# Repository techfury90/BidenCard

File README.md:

# Biden Card
Partially cost reduced/modernized Sinclair QL Trump Card clone with bonus Dark Brandon meme.

# Background
I originally started this project in late 2023 because real Trump Cards were getting difficult to obtain, and I wanted one for my QLs. 

Alvaro had previously successfully cloned the board, but there were timing-related issues with substituting the PALs for GALs. Analysis of the situation revealed that the issue related to DRAM control timing. Since 41256 DRAM is no longer made, I decided to move to AS6C4008 4mbit SRAM. The resulting logic simplification also eliminated the need for GAL 2, and paring down GAL 1's DRAM-related functions allowed me to fit the new SRAM decode logic into GAL 1, thereby eliminating GAL 2 entirely. 

The end result is 100% compatible with the Trump Card, but only costs about $50 USD to manufacture.

This design is a bit quick/rudimentary/slapdash- in particular, these low-hanging fruits exist for optimization: 
- Replace DIP AS6C4008s with suitable SMD SRAM. Do note that I grounded out OE (output enable) and use only CS to access the SRAM- most SRAMs can handle this but please check the datasheet!
- Redo axial caps with radials (this was really just cargo-culted from the original design to get a viable prototype working quickly)
- Replace 7805 with a more efficient regulator (even with the 7805, however, power consumption is a fraction of the original Trump Card!)

# Credits
- Alvaro Alea for reverse engineering the Trump Card 2 schematic (the basis of this project)
- Tetroid for reverse engineering the PAL/GAL logic equations. His equations were the basis of mine, particularly in regards to the P13/P16 ROM shadowing bodge needed to make pre-Minerva ROMs recognize the ROM.
- Compgeke for doing the PCB layout (I have not quite honed that skill yet... this is my first DIY PCB project of this scale!)

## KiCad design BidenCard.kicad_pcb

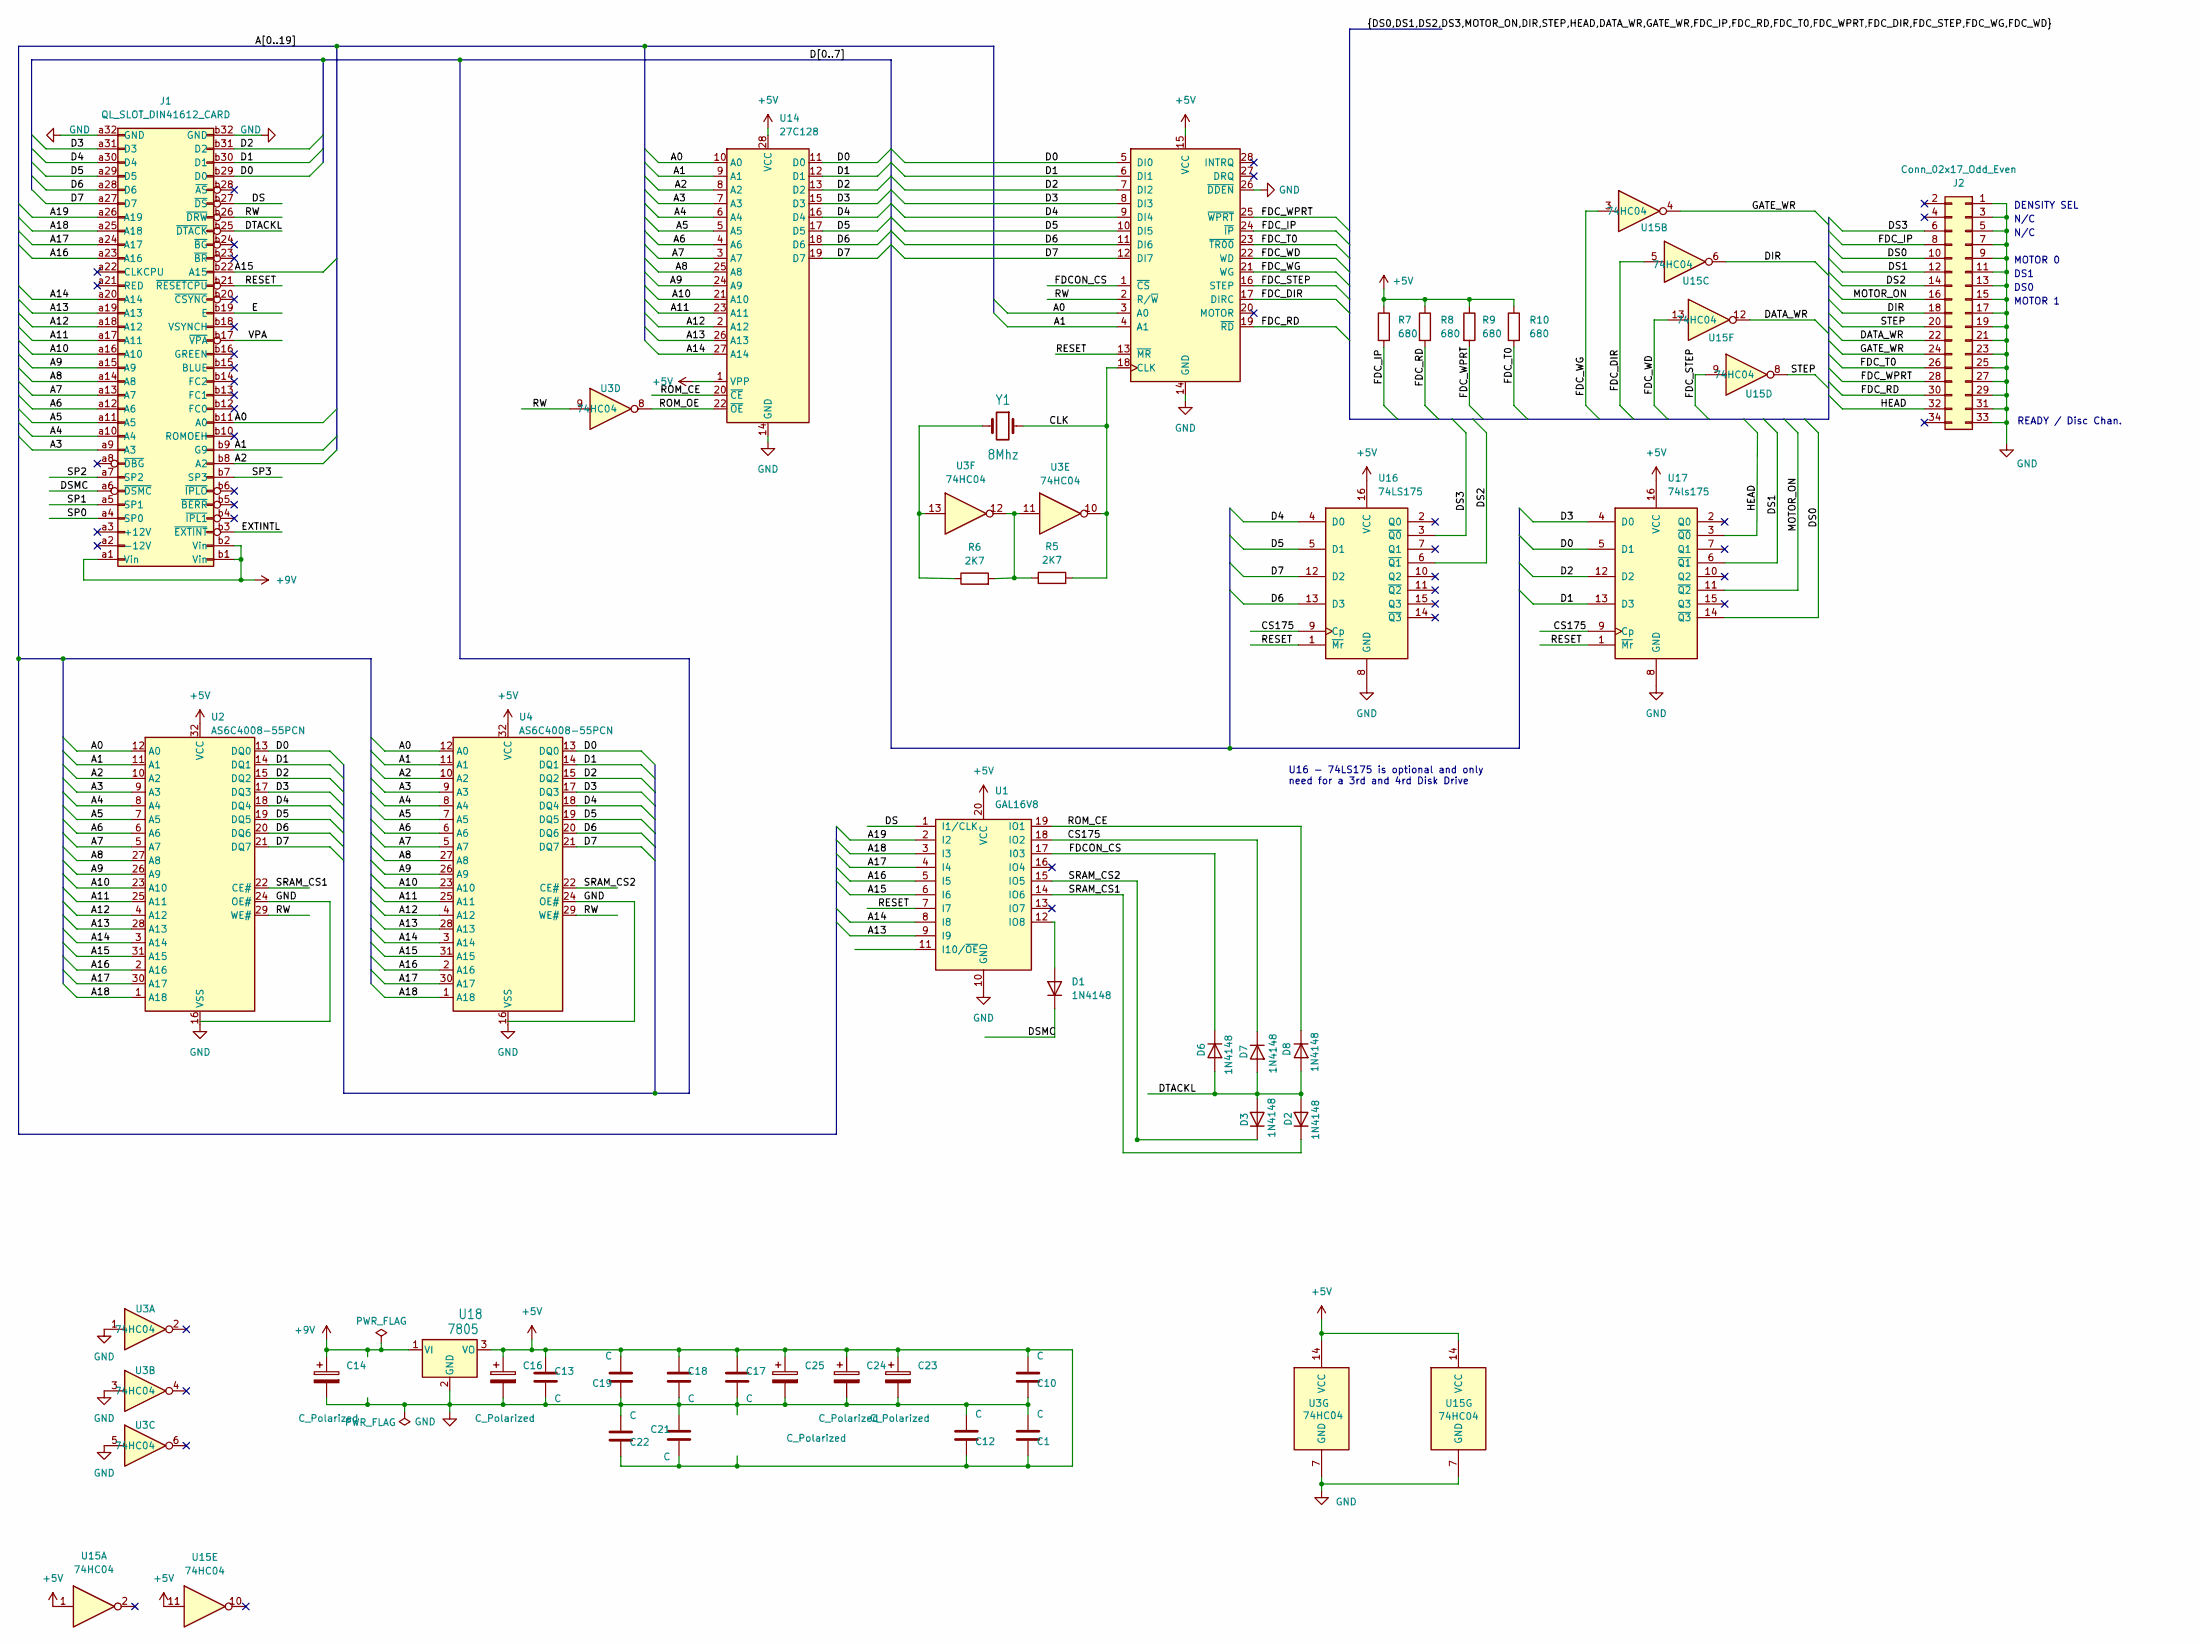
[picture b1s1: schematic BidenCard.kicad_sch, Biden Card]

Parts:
C1, C10, C12, C17, C18, C19, C21, C22: C; C_Disc_D7.5mm_W4.4mm_P5.00mm
C13: C; C_Disc_D5.1mm_W3.2mm_P5.00mm
C14, C16, C23, C24, C25: C_Polarized; CP_Axial_L11.0mm_D5.0mm_P18.00mm_Horizontal
D1, D2, D3, D6, D7, D8: 1N4148; D_DO-35_SOD27_P10.16mm_Horizontal
J1: QL_SLOT_DIN41612_CARD; DIN41612_B_2x32_Male_Horizontal_THT
J2: Conn_02x17_Odd_Even; PinHeader_2x17_P2.54mm_Horizontal
R5, R6: 2K7; R_Axial_DIN0207_L6.3mm_D2.5mm_P10.16mm_Horizontal
R7, R8, R9, R10: 680; R_Axial_DIN0207_L6.3mm_D2.5mm_P10.16mm_Horizontal
U1: GAL16V8; DIP-20_W7.62mm
U2, U4: AS6C4008-55PCN; DIP-32_W15.24mm
U3, U15: 74HC04; DIP-14_W7.62mm
U13: FDC_WD1772; DIP-28_W15.24mm
U14: 27C128; DIP-28_W15.24mm
U16: 74LS175; DIP-16_W7.62mm
U17: 74ls175; DIP-16_W7.62mm
U18: 7805; TO-220-3_Horizontal_TabDown
Y1: 8Mhz; Crystal_HC18-U_Vertical

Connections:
+5V: C1.1, C10.2, C12.1, C13.1, C16.1, C17.1, C18.1, C19.2, C21.2, C22.1, C23.1, C24.1, C25.1, R7.1, R8.1, R9.1, R10.1, U1.20 (VCC), U2.32 (VCC), U3.14 (VCC), U4.32 (VCC), U13.15 (VCC), U14.1 (VPP), U14.28 (VCC), U15.1, U15.11, U15.14 (VCC), U16.16 (VCC), U17.16 (VCC), U18.3 (VO)
+9V: C14.1, J1.a1 (Vin), J1.b1 (Vin), J1.b2 (Vin), U18.1 (VI)
/A0: J1.b11 (A0), U2.12 (A0), U4.12 (A0), U13.3 (A0), U14.10 (A0)
/A1: J1.b9 (G9), U2.11 (A1), U4.11 (A1), U13.4 (A1), U14.9 (A1)
/A2: J1.b8 (A2), U2.10 (A2), U4.10 (A2), U14.8 (A2)
/A3: J1.a9 (A3), U2.9 (A3), U4.9 (A3), U14.7 (A3)
/A4: J1.a10 (A4), U2.8 (A4), U4.8 (A4), U14.6 (A4)
/A5: J1.a11 (A5), U2.7 (A5), U4.7 (A5), U14.5 (A5)
/A6: J1.a12 (A6), U2.6 (A6), U4.6 (A6), U14.4 (A6)
/A7: J1.a13 (A7), U2.5 (A7), U4.5 (A7), U14.3 (A7)
/A8: J1.a14 (A8), U2.27 (A8), U4.27 (A8), U14.25 (A8)
/A9: J1.a15 (A9), U2.26 (A9), U4.26 (A9), U14.24 (A9)
/A10: J1.a16 (A10), U2.23 (A10), U4.23 (A10), U14.21 (A10)
/A11: J1.a17 (A11), U2.25 (A11), U4.25 (A11), U14.23 (A11)
/A12: J1.a18 (A12), U2.4 (A12), U4.4 (A12), U14.2 (A12)
/A13: J1.a19 (A13), U1.9 (I9), U2.28 (A13), U4.28 (A13), U14.26 (A13)
/A14: J1.a20 (A14), U1.8 (I8), U2.3 (A14), U4.3 (A14), U14.27 (A14)
/A15: J1.b22 (A15), U1.6 (I6), U2.31 (A15), U4.31 (A15)
/A16: J1.a23 (A16), U1.5 (I5), U2.2 (A16), U4.2 (A16)
/A17: J1.a24 (A17), U1.4 (I4), U2.30 (A17), U4.30 (A17)
/A18: J1.a25 (A18), U1.3 (I3), U2.1 (A18), U4.1 (A18)
/A19: J1.a26 (A19), U1.2 (I2)
/CLK: R5.2, U3.10, U13.18 (CLK), Y1.1
/CS175: D7.1 (K), U1.18 (IO2), U16.9 (Cp), U17.9 (Cp)
/D0: J1.b29 (D0), U2.13 (DQ0), U4.13 (DQ0), U13.5 (DI0), U14.11 (D0), U17.5 (D1)
/D1: J1.b30 (D1), U2.14 (DQ1), U4.14 (DQ1), U13.6 (DI1), U14.12 (D1), U17.13 (D3)
/D2: J1.b31 (D2), U2.15 (DQ2), U4.15 (DQ2), U13.7 (DI2), U14.13 (D2), U17.12 (D2)
/D3: J1.a31 (D3), U2.17 (DQ3), U4.17 (DQ3), U13.8 (DI3), U14.15 (D3), U17.4 (D0)
/D4: J1.a30 (D4), U2.18 (DQ4), U4.18 (DQ4), U13.9 (DI4), U14.16 (D4), U16.4 (D0)
/D5: J1.a29 (D5), U2.19 (DQ5), U4.19 (DQ5), U13.10 (DI5), U14.17 (D5), U16.5 (D1)
/D6: J1.a28 (D6), U2.20 (DQ6), U4.20 (DQ6), U13.11 (DI6), U14.18 (D6), U16.13 (D3)
/D7: J1.a27 (D7), U2.21 (DQ7), U4.21 (DQ7), U13.12 (DI7), U14.19 (D7), U16.12 (D2)
/DATA_WR: J2.22, U15.12
/DIR: J2.18, U15.6
/DS: J1.b27 (~DS), U1.1 (I1/CLK)
/DS0: J2.10, U17.14 (~Q3)
/DS1: J2.12, U17.6 (~Q1)
/DS2: J2.14, U16.6 (~Q1)
/DS3: J2.6, U16.3 (~Q0)
/DSMC: D1.1 (K), J1.a6 (~DSMC)
/DTACKL: D2.2 (A), D3.2 (A), D6.2 (A), D7.2 (A), D8.2 (A), J1.b25 (~DTACK)
/E: J1.b19 (E)
/EXTINTL: J1.b3 (~EXTINT)
/FDCON_CS: D6.1 (K), U1.17 (I03), U13.1 (~CS)
/FDC_DIR: U13.17 (DIRC), U15.5
/FDC_IP: J2.8, R7.2, U13.24 (~IP)
/FDC_RD: J2.30, R8.2, U13.19 (~RD)
/FDC_STEP: U13.16 (STEP), U15.9
/FDC_T0: J2.26, R10.2, U13.23 (~TR00)
/FDC_WD: U13.22 (WD), U15.13
/FDC_WG: U13.21 (WG), U15.3
/FDC_WPRT: J2.28, R9.2, U13.25 (~WPRT)
/GATE_WR: J2.24, U15.4
/HEAD: J2.32, U17.3 (~Q0)
/MOTOR_ON: J2.16, U17.11 (~Q2)
/RESET: J1.b21 (~RESETCPU), U1.7 (I7), U13.13 (~MR), U16.1 (~Mr), U17.1 (~Mr)
/ROM_CE: D8.1 (K), U1.19 (IO1), U14.20 (~CE)
/ROM_OE: U3.8, U14.22 (~OE)
/RW: J1.b26 (~DRW), U2.29 (WE#), U3.9, U4.29 (WE#), U13.2 (R/~W)
/SP0: J1.a4 (SP0)
/SP1: J1.a5 (SP1)
/SP2: J1.a7 (SP2)
/SP3: J1.b7 (SP3)
/SRAM_CS1: D2.1 (K), U1.14 (IO6), U2.22 (CE#)
/SRAM_CS2: D3.1 (K), U1.15 (IO5), U4.22 (CE#)
/STEP: J2.20, U15.8
/VPA: J1.b17 (~VPA)
GND: C1.2, C10.1, C12.2, C13.2, C14.2, C16.2, C17.2, C18.2, C19.1, C21.1, C22.2, C23.2, C24.2, C25.2, J1.a32 (GND), J1.b32 (GND), J2.1, J2.3, J2.5, J2.7, J2.9, J2.11, J2.13, J2.15, J2.17, J2.19, J2.21, J2.23, J2.25, J2.27, J2.29, J2.31, J2.33, U1.10 (GND), U2.16 (VSS), U2.24 (OE#), U3.1, U3.3, U3.5, U3.7 (GND), U4.16 (VSS), U4.24 (OE#), U13.14 (GND), U13.26 (~DDEN), U14.14 (GND), U15.7 (GND), U16.8 (GND), U17.8 (GND), U18.2 (GND)
unnamed: D1.2 (A), U1.12 (IO8)
unnamed: R5.1, R6.2, U3.11, U3.12
unnamed: R6.1, U3.13, Y1.2

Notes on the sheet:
MOTOR 0
DS0
DS1
READY / Disc Chan.
MOTOR 1
U16 - 74LS175 is optional and only need for a 3rd and 4rd Disk Drive
N/C
DENSITY SEL

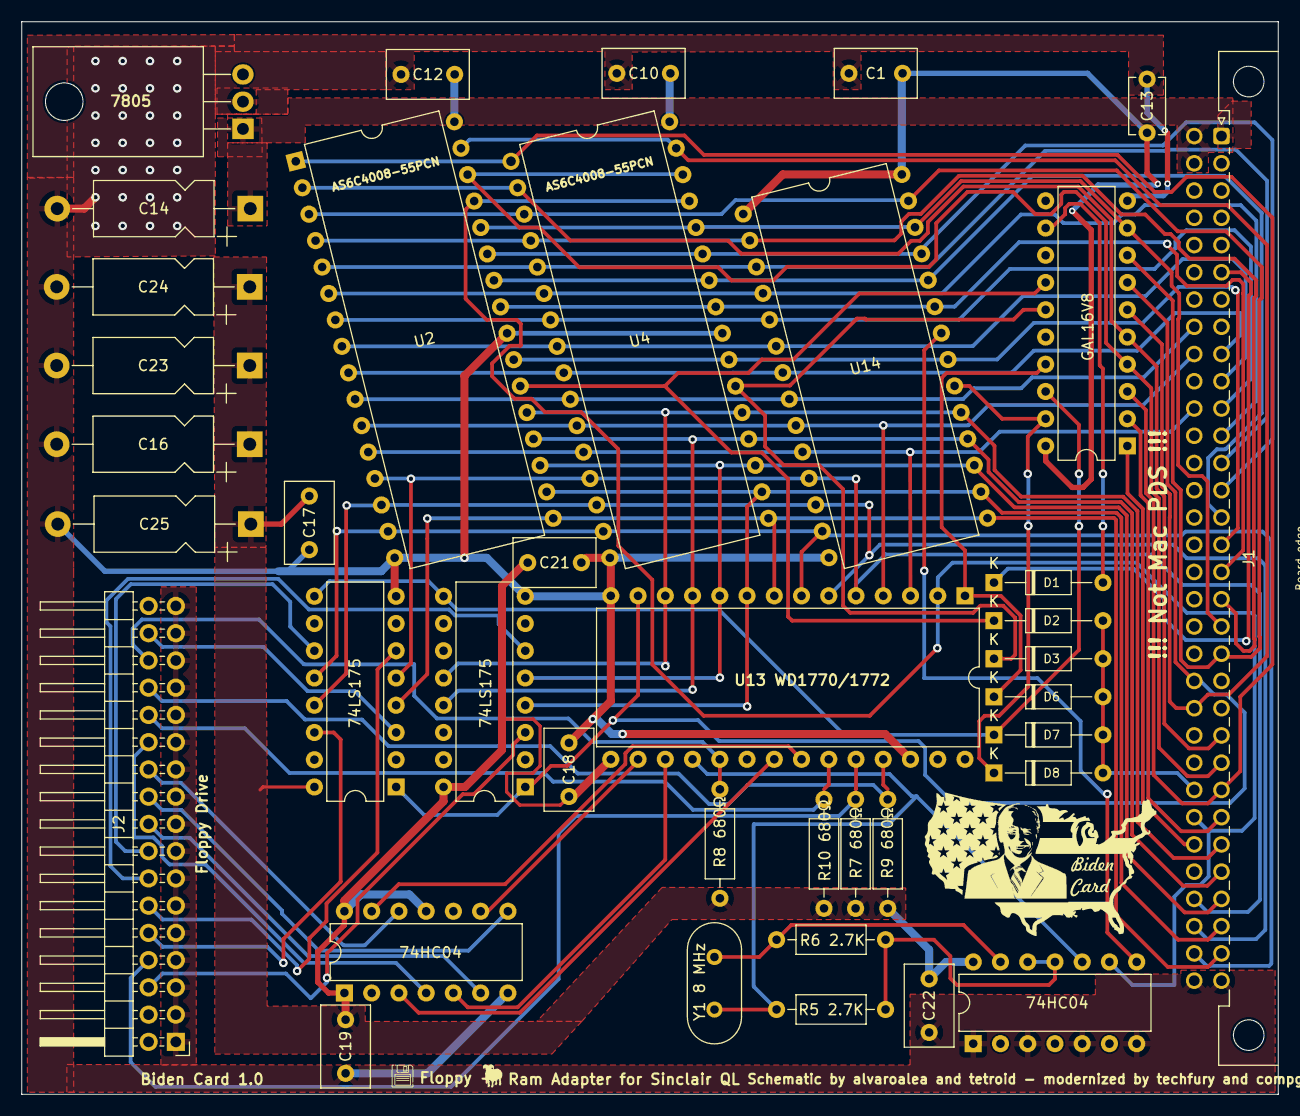
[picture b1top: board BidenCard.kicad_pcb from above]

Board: 2 copper layers, 117.2 x 100.0 mm, 39 parts (0 on the bottom side), 64 nets.

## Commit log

2025-03-11 add project (with ECO for U3)
2025-03-11 add GAL WinCUPL source
2025-03-11 update PCB silkscreen for revision 2
2025-03-11 add Gerbers for JLC fabrication
2025-03-11 add photo of assembled card
2025-03-11 shrink photo
